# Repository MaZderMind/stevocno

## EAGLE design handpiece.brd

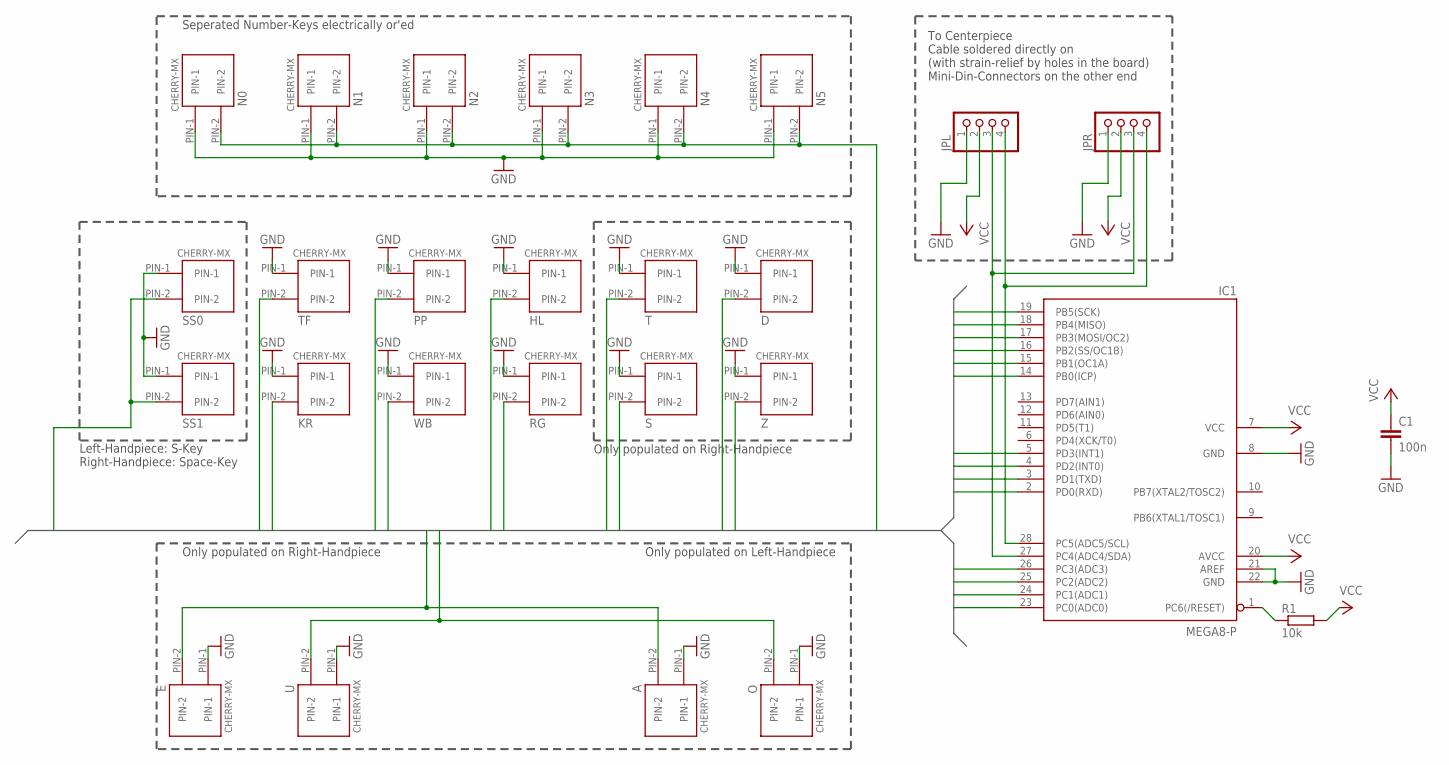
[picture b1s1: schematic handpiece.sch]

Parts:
A: CHERRY-MX-I
C1: 100n; C075-032X103
D: CHERRY-MX-I
E: CHERRY-MX-I
HL: CHERRY-MX-I
IC1: MEGA8-P; DIL28-3
JPL: PINHD-1X4; 1X04
JPR: PINHD-1X4; 1X04
KR: CHERRY-MX-I
N0, N1, N2, N3, N4, N5: CHERRY-MX-I
O: CHERRY-MX-I
PP: CHERRY-MX-I
R1: 10k; 0207/7
RG: CHERRY-MX-I
S: CHERRY-MX-I
SS0, SS1: CHERRY-MX-I
T: CHERRY-MX-I
TF: CHERRY-MX-I
U: CHERRY-MX-I
WB: CHERRY-MX-I
Z: CHERRY-MX-I

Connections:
D: D.PIN-2, IC1.15 (PB1(OC1A))
EA: A.PIN-2, E.PIN-2, IC1.4 (PD2(INT0))
GND: A.PIN-1, C1.2, D.PIN-1, E.PIN-1, HL.PIN-1, IC1.8 (GND), IC1.21 (AREF), IC1.22 (GND), JPL.1, JPR.1, KR.PIN-1, N0.PIN-1, N1.PIN-1, N2.PIN-1, N3.PIN-1, N4.PIN-1, N5.PIN-1, O.PIN-1, PP.PIN-1, RG.PIN-1, S.PIN-1, SS0.PIN-1, SS1.PIN-1, T.PIN-1, TF.PIN-1, U.PIN-1, WB.PIN-1, Z.PIN-1
HL: HL.PIN-2, IC1.23 (PC0(ADC0))
KR: IC1.2 (PD0(RXD)), KR.PIN-2
N: IC1.14 (PB0(ICP)), N0.PIN-2, N1.PIN-2, N2.PIN-2, N3.PIN-2, N4.PIN-2, N5.PIN-2
unnamed: IC1.1 (PC6(/RESET)), R1.1
OU: IC1.5 (PD3(INT1)), O.PIN-2, U.PIN-2
PP: IC1.24 (PC1(ADC1)), PP.PIN-2
RG: IC1.19 (PB5(SCK)), RG.PIN-2
S: IC1.17 (PB3(MOSI/OC2)), S.PIN-2
SCL: IC1.28 (PC5(ADC5/SCL)), JPL.4, JPR.4
SDA: IC1.27 (PC4(ADC4/SDA)), JPL.3, JPR.3
SS: IC1.3 (PD1(TXD)), SS0.PIN-2, SS1.PIN-2
T: IC1.18 (PB4(MISO)), T.PIN-2
TF: IC1.26 (PC3(ADC3)), TF.PIN-2
VCC: C1.1, IC1.7 (VCC), IC1.20 (AVCC), JPL.2, JPR.2, R1.2
WB: IC1.25 (PC2(ADC2)), WB.PIN-2
Z: IC1.16 (PB2(SS/OC1B)), Z.PIN-2

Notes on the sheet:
Seperated Number-Keys electrically or'ed
Left-Handpiece: S-Key Right-Handpiece: Space-Key
Only populated on Right-Handpiece
Only populated on Left-Handpiece
To Centerpiece Cable soldered directly on (with strain-relief by holes in the board) Mini-Din-Connectors on the other end

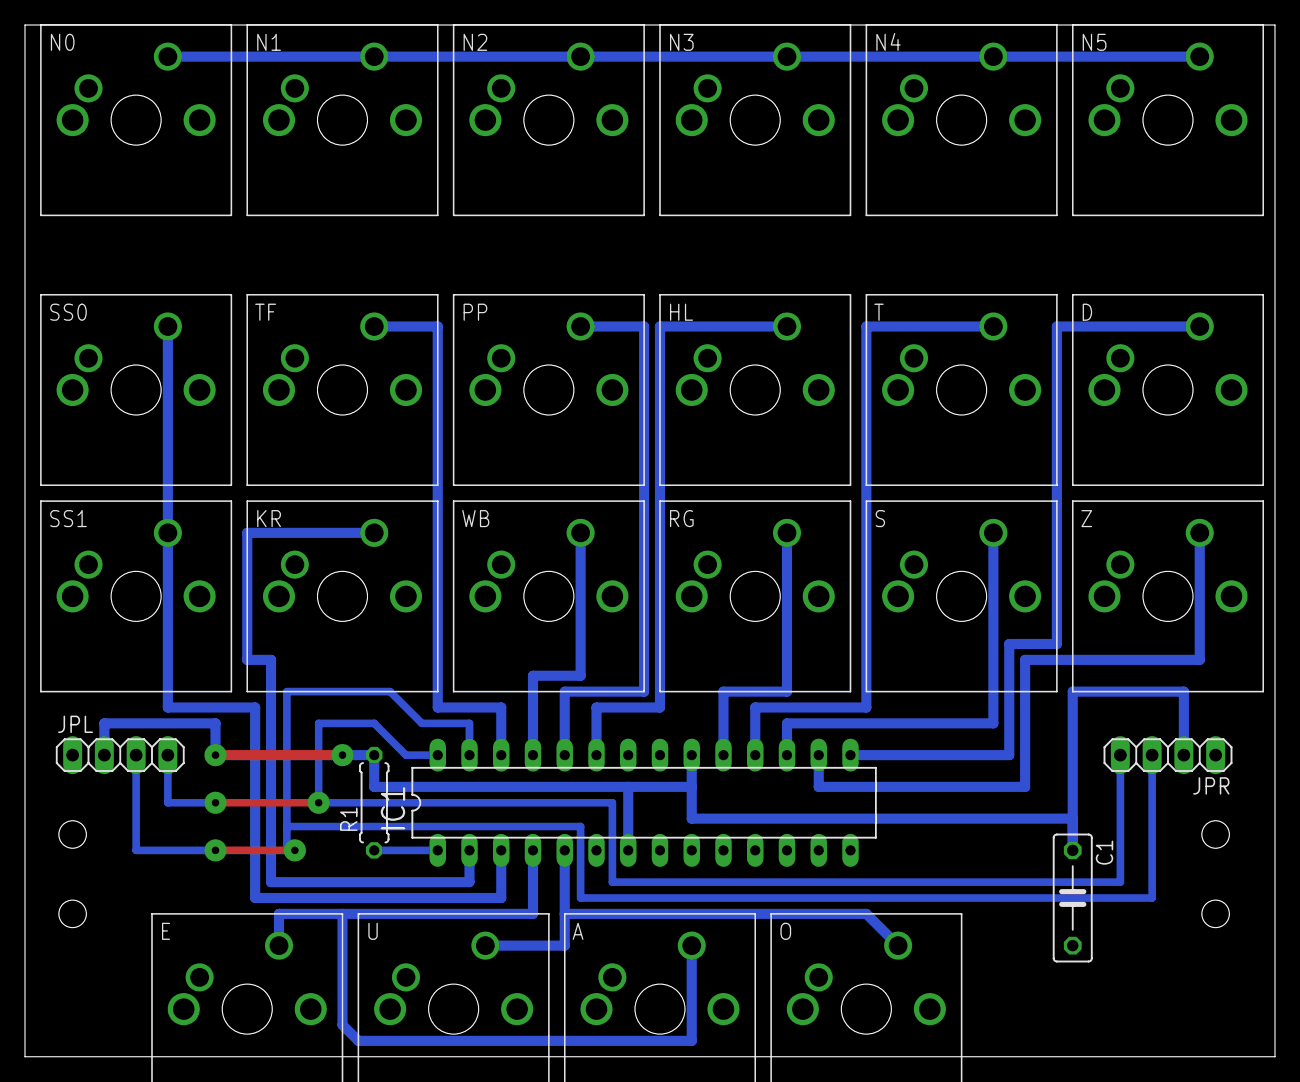
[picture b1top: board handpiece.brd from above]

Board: 2 copper layers, 100.0 x 82.5 mm, 27 parts (0 on the bottom side), 19 nets.

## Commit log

2014-07-13 initial commit of handpiece with cherry keys
2014-07-13 text marker besides con
2014-07-13 proof of concept routing
2014-07-14 add second connector (only one populated on one board)
2014-07-14 wire i²c
2014-07-17 add name & value to the crerry-keys (helps identify them on the board)
2014-07-17 move vocal keys to comply to https://sites.google.com/site/ploverdoc/lesson-1-fingers-and-keys
2014-07-17 exchange minidin connectors with raw soldering pads and strain-releive holes
2014-07-17 fix groundplane placement
2014-07-17 fix trace widths
2014-07-17 add pdfs for better accessability
